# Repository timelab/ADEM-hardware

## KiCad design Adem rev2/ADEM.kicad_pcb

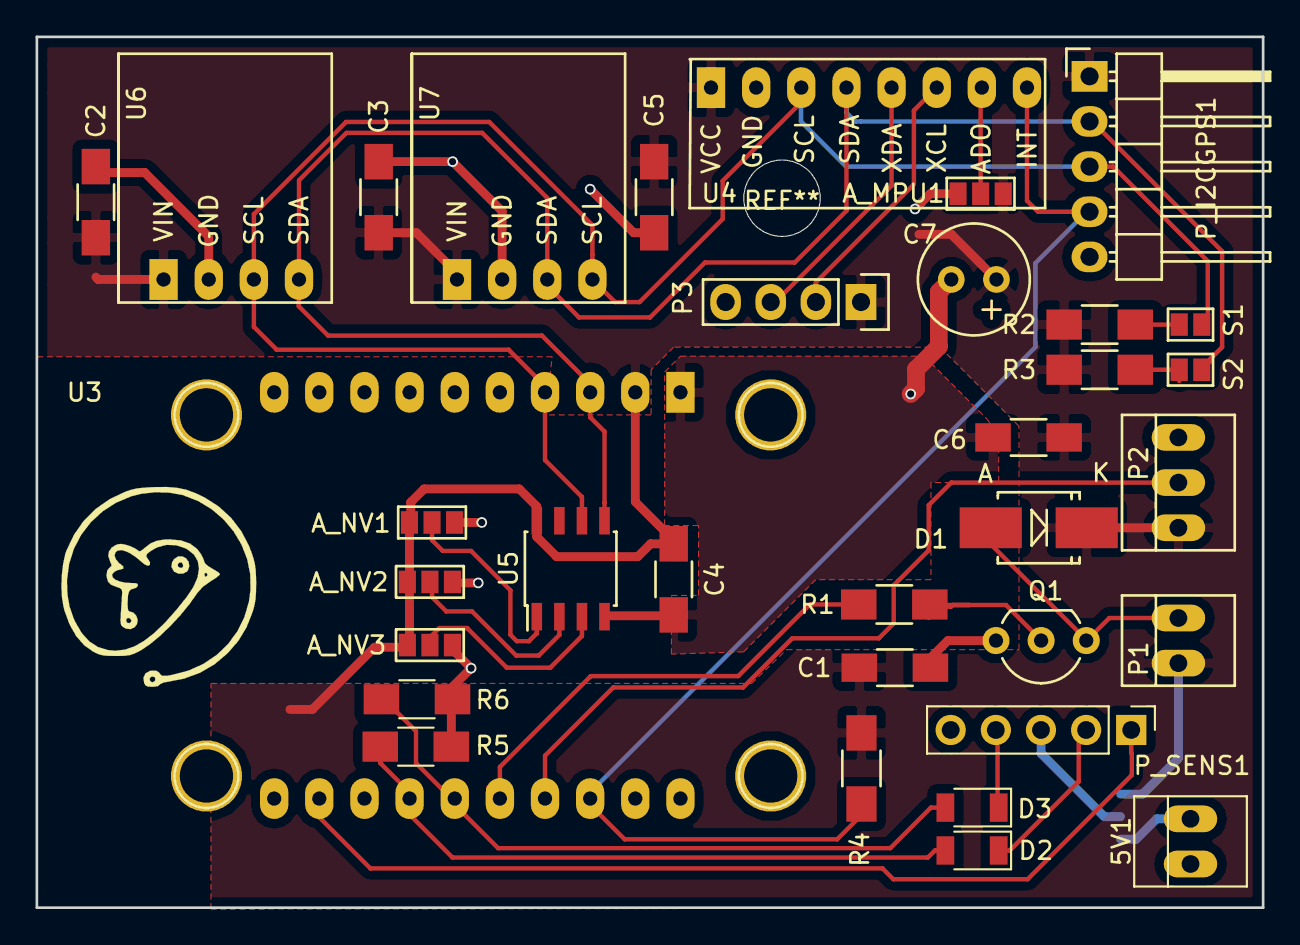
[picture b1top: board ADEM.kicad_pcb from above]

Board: 2 copper layers, 69.0 x 49.0 mm, 35 parts (1 on the bottom side), 24 nets.

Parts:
5V1: 5V; PINHEAD1-2
A_MPU1: GS_A0; GS3
A_NV1: GS_A0; GS3
A_NV2: GS_A1; GS3
A_NV3: GS_A2; GS3
C1, C2, C3, C4, C5, C6: C; C_1206_HandSoldering
C7: CP; Elko_vert_11.2x6.3mm_RM2.5
D1: DIODE; SMB_Handsoldering
D2, D3: 1V8; D_1206
P1: CONN_buzz; PINHEAD1-2
P2: CONN_01X03; PINHEAD1-3
P3: CONN_01X04; Pin_Header_Straight_1x04
P_I2CGPS1: CONN_01X05; Pin_Header_Angled_1x05
P_SENS1: CONN_01X05; Pin_Header_Straight_1x05_Pitch2.54mm
Q1: NPN; TO-92_Inline_Wide
R1, R2, R3, R4: R; R_1206_HandSoldering
R5, R6: 10K; R_1206_HandSoldering
S1: S1; GS2
S2: S2; GS2
U3: ESP8266_THING
U4: MPU6050; MPU6050_angled
U5: NVSRAM; SOIC-8_3.9x4.9mm_Pitch1.27mm
U6: BMP180
U7: HTU21D
VCC_SEL1: GS_VCC; GS3

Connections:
A_SENSOR: P_SENS1.1, U3.12
BUZZ: R1.1, U3.16
GND: 5V1.1, A_MPU1.3, A_NV1.3, A_NV2.3, A_NV3.3, C1.2, C2.2, C3.2, C4.2, C5.2, C6.2, C7.2, P2.3, P3.4, P_I2CGPS1.5, P_SENS1.5, Q1.3, R5.2, R6.2, U3.1, U3.10, U3.20, U4.2, U5.4, U6.2, U7.2
INT: P_I2CGPS1.4, R4.2, U3.18, U4.8
NEO_PXL: P2.2, U3.17
unnamed: 5V1.2, VCC_SEL1.3
unnamed: A_MPU1.2, U4.7
unnamed: A_NV1.2, U5.1
unnamed: A_NV2.2, U5.2
unnamed: A_NV3.2, U5.3
unnamed: D1.2, P1.2, Q1.1
unnamed: P3.2, U4.6
unnamed: P3.3, U4.5
unnamed: P_SENS1.3, VCC_SEL1.2
unnamed: Q1.2, R1.2
unnamed: R2.2, S1.1
unnamed: R3.1, S2.2
P10_SENS: D2.1, P_SENS1.2
P10_SENS_SHFT: D2.2, R5.1, U3.14
P25_SENS: D3.1, P_SENS1.4
P25_SENS_SHFT: D3.2, R6.1, U3.15
SCL: P_I2CGPS1.3, S1.2, U3.4, U4.3, U5.6, U6.3, U7.4
SDA: P_I2CGPS1.2, S2.1, U3.3, U4.4, U5.5, U6.4, U7.3
VCC: A_MPU1.1, A_NV1.1, A_NV2.1, A_NV3.1, C1.1, C2.1, C3.1, C4.1, C5.1, C6.1, C7.1, D1.1, P1.1, P2.1, P3.1, P_I2CGPS1.1, R2.1, R3.2, R4.1, U3.2, U4.1, U5.8, U6.1, U7.1, VCC_SEL1.1

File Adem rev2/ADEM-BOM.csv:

"Id";"Designator";"Package";"Quantity";"Designation";"Supplier and ref";
1;"U3";"ESP8266_THING";1;"ESP8266_THING";;;
2;"REF**";"MountingHole_4.3mm_M4";1;"MountingHole_4.3mm_M4";;;
3;"U7";"HTU21D";1;"HTU21D";;;
4;"R3,R1,R2,R4";"R_1206_HandSoldering";4;"R";;;
5;"C1,C2,C3,C4,C5,C6";"C_1206_HandSoldering";6;"C";;;
6;"D1";"SMB_Handsoldering";1;"DIODE";;;
7;"P1";"PINHEAD1-2";1;"CONN_buzz";;;
8;"Q1";"TO-92_Inline_Wide";1;"NPN";;;
9;"U5";"SOIC-8_3.9x4.9mm_Pitch1.27mm";1;"NVSRAM";;;
10;"U6";"BMP180";1;"BMP180";;;
11;"P2";"PINHEAD1-3";1;"CONN_01X03";;;
12;"P3";"Pin_Header_Straight_1x04";1;"CONN_01X04";;;
13;"C7";"Elko_vert_11.2x6.3mm_RM2.5";1;"CP";;;
14;"S2";"GS2";1;"S2";;;
15;"P_I2CGPS1";"Pin_Header_Angled_1x05";1;"CONN_01X05";;;
16;"A_MPU1,A_NV1";"GS3";2;"GS_A0";;;
17;"A_NV2";"GS3";1;"GS_A1";;;
18;"A_NV3";"GS3";1;"GS_A2";;;
19;"S1";"GS2";1;"S1";;;
20;"U4";"MPU6050_angled";1;"MPU6050";;;
21;"";"adem_logo";1;"";;;
22;"";"adem_logo-txt_17_B_silk";1;"";;;
23;"5V1";"PINHEAD1-2";1;"5V";;;
24;"D2,D3";"D_1206";2;"1V8";;;
25;"R5,R6";"R_1206_HandSoldering";2;"10K";;;
26;"P_SENS1";"Pin_Header_Straight_1x05_Pitch2.54mm";1;"CONN_01X05";;;
27;"VCC_SEL1";"GS3";1;"GS_VCC";;;

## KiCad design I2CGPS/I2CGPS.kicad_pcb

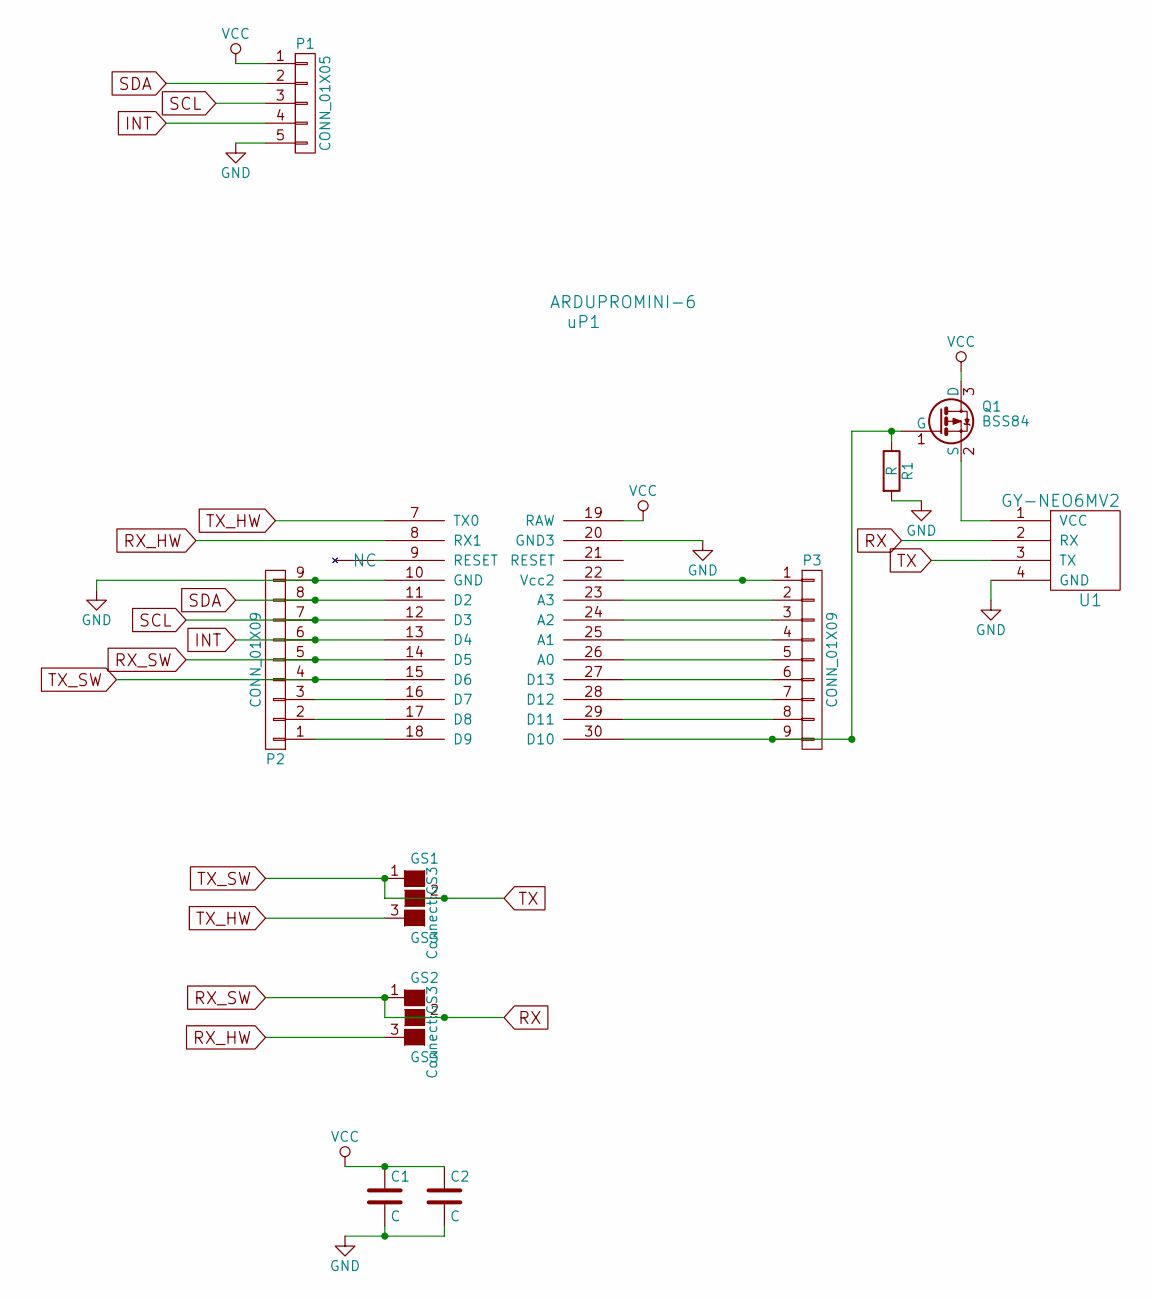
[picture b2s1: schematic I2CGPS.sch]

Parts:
C1, C2: C; C_1210_HandSoldering
GS1, GS2: GS3
P1: CONN_01X05; Pin_Header_Angled_1x05
P2, P3: CONN_01X09; Pin_Header_Straight_1x09
Q1: BSS84; SOT-23
R1: R; R_1210_HandSoldering
U1: GY-NEO6MV2
uP1: ARDUPROMINI-6; ArduProMini

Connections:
GND: C1.2, C2.2, P1.5, P2.9, R1.2, U1.4 (GND), uP1.10 (GND), uP1.20 (GND3)
INT: P1.4, P2.6, uP1.13 (D4)
unnamed: P2.1, uP1.18 (D9)
unnamed: P2.2, uP1.17 (D8)
unnamed: P2.3, uP1.16 (D7)
unnamed: P3.1, uP1.22 (Vcc2)
unnamed: P3.2, uP1.23 (A3)
unnamed: P3.3, uP1.24 (A2)
unnamed: P3.4, uP1.25 (A1)
unnamed: P3.5, uP1.26 (A0)
unnamed: P3.6, uP1.27 (D13)
unnamed: P3.7, uP1.28 (D12)
unnamed: P3.8, uP1.29 (D11)
unnamed: P3.9, Q1.1 (G), R1.1, uP1.30 (D10)
unnamed: Q1.2 (S), U1.1 (VCC)
RX: GS2.1 (G1), GS2.2 (G2), P2.5, U1.2 (RX), uP1.14 (D5)
RX_HW: GS2.3 (G3), uP1.8 (RX1)
SCL: P1.3, P2.7, uP1.12 (D3)
SDA: P1.2, P2.8, uP1.11 (D2)
TX: GS1.1 (G1), GS1.2 (G2), P2.4, U1.3 (TX), uP1.15 (D6)
TX_HW: GS1.3 (G3), uP1.7 (TX0)
VCC: C1.1, C2.1, P1.1, Q1.3 (D), uP1.19 (RAW)

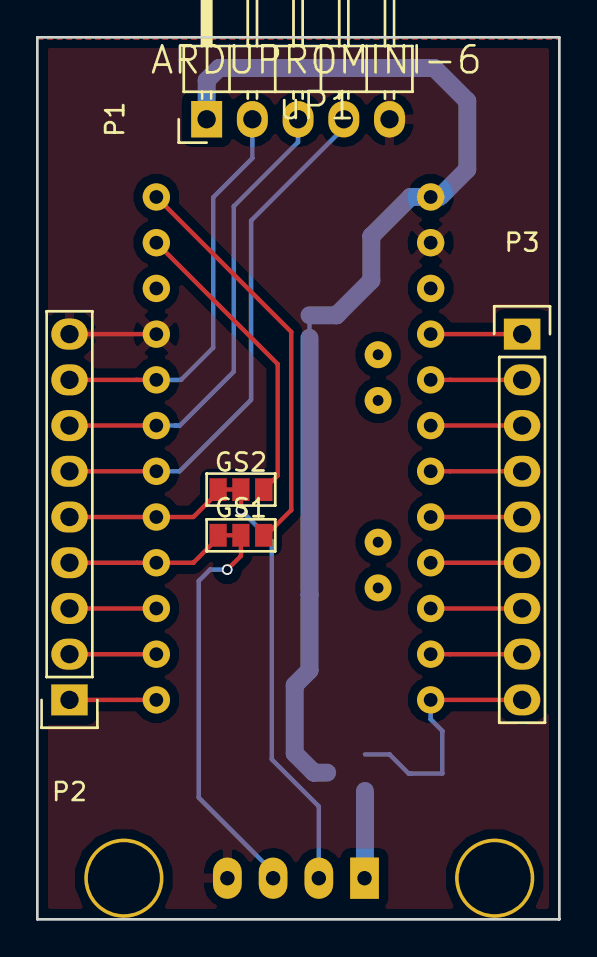
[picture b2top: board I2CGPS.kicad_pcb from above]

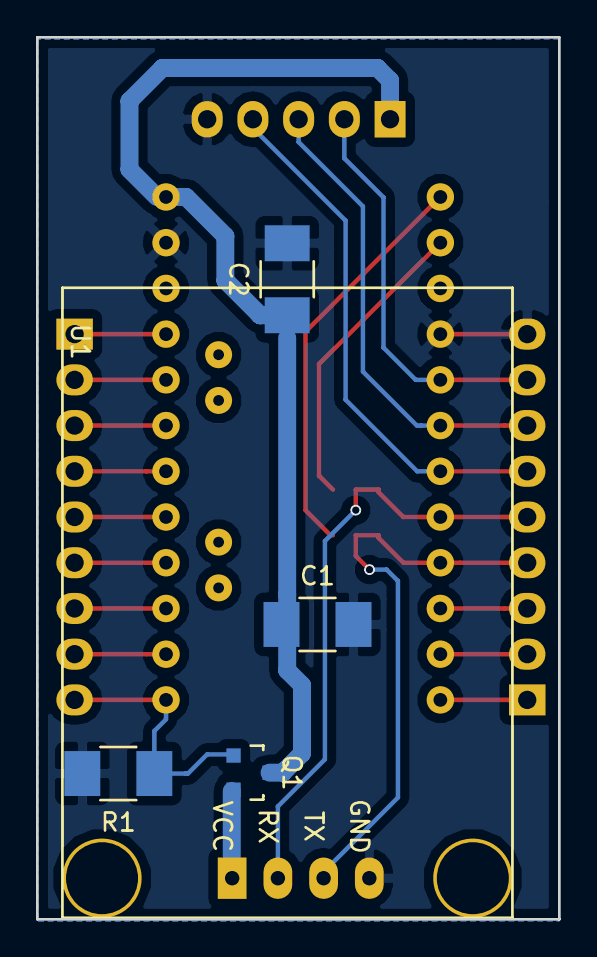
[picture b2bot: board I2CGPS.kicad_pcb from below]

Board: 2 copper layers, 29.0 x 49.0 mm, 11 parts (5 on the bottom side), 22 nets.

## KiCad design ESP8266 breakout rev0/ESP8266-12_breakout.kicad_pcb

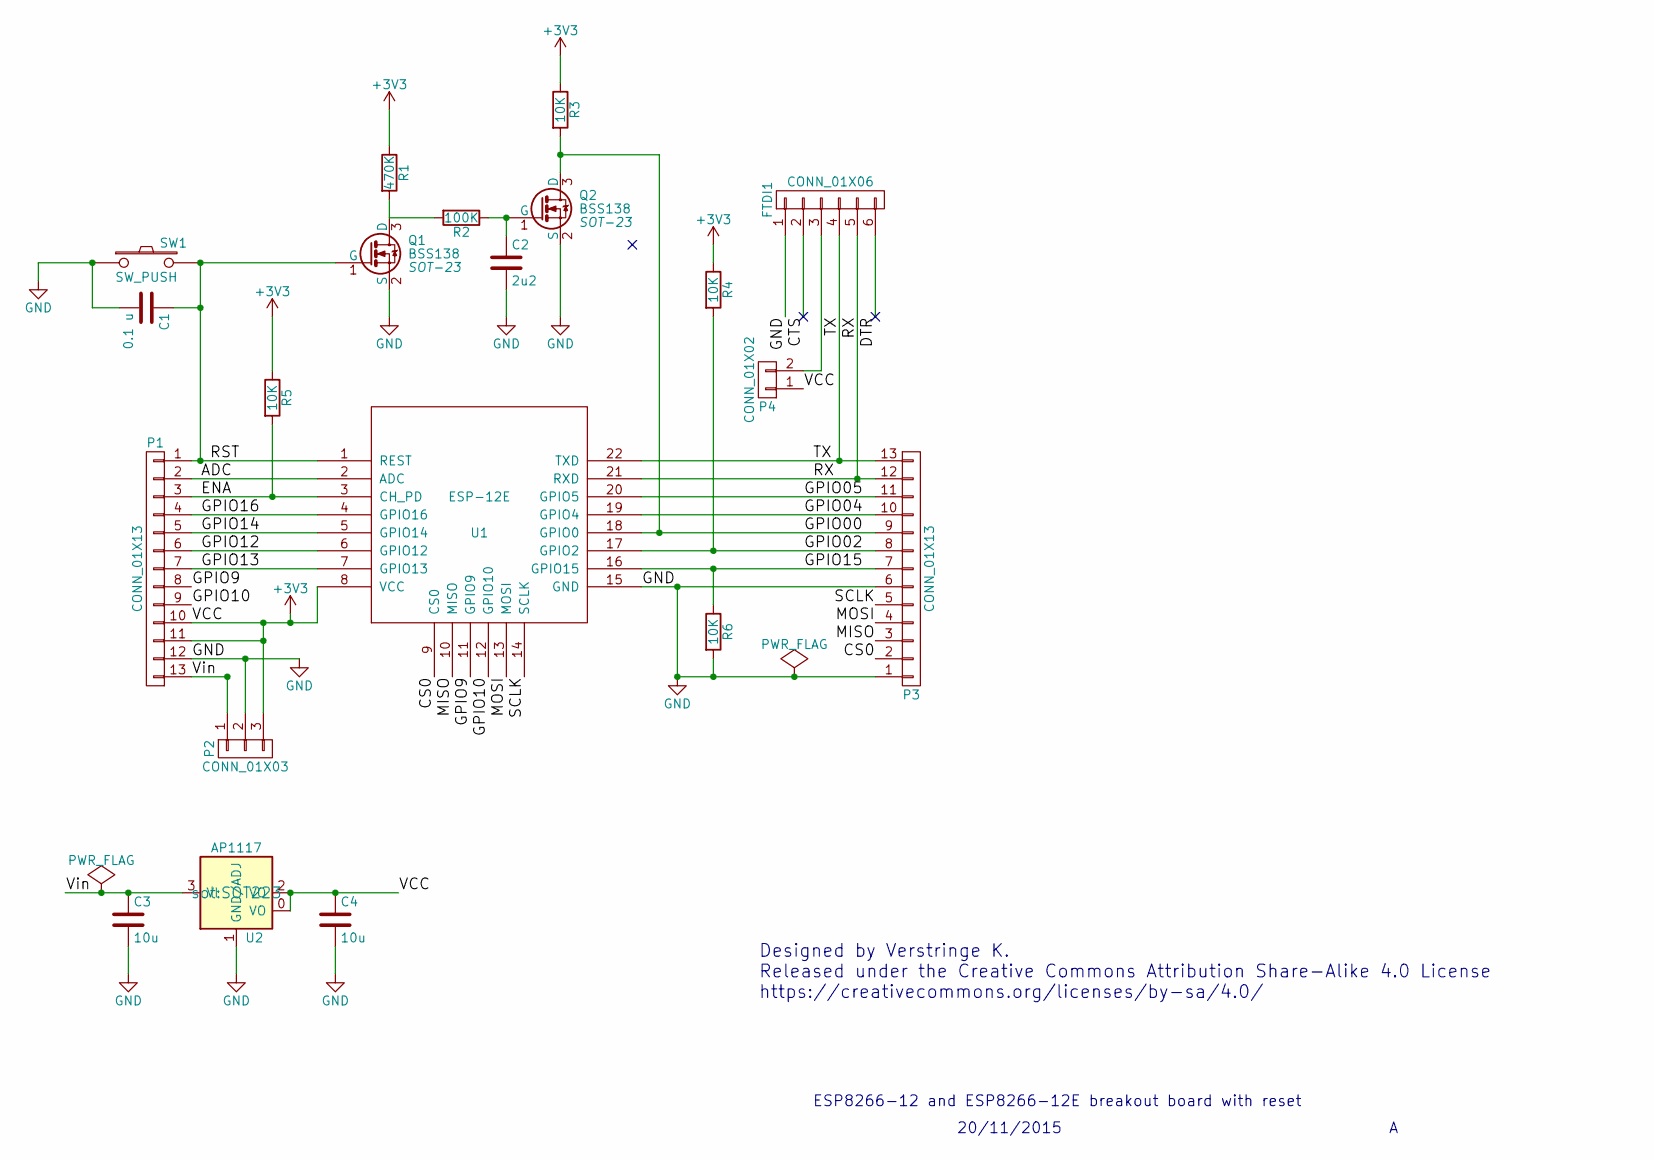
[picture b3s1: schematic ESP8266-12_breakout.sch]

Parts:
C1: 0.1 u; C_1206_HandSoldering
C2: 2u2; C_1206_HandSoldering
C3, C4: 10u; C_1206_HandSoldering
FTDI1: CONN_01X06; Pin_Header_Straight_1x06
P1, P3: CONN_01X13; Pin_Header_Straight_1x13
P2: CONN_01X03; Pin_Header_Straight_1x03
P4: CONN_01X02; Pin_Header_Straight_1x02
Q1, Q2: BSS138; SOT-23
R1: 470K; R_1206_HandSoldering
R2: 100K; R_1206_HandSoldering
R3, R4, R5, R6: 10K; R_1206_HandSoldering
SW1: SW_PUSH; SW_SPST_EVPBF
U1: ESP-12E
U2: AP1117; SOT223

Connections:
+3V3: C4.1, P1.10, P1.11, P2.3, P4.1, R1.1, R3.1, R4.1, R5.1, U1.8 (VCC), U2.0 (VO), U2.2 (VO)
/ADC: P1.2, U1.2 (ADC)
/CS0: P3.2, U1.9 (CS0)
/CTS: FTDI1.2
/DTR: FTDI1.6
/ENA: P1.3, R5.2, U1.3 (CH_PD)
/GPIO00: P3.9, Q2.3 (D), R3.2, U1.18 (GPIO0)
/GPIO02: P3.8, R4.2, U1.17 (GPIO2)
/GPIO04: P3.10, U1.19 (GPIO4)
/GPIO05: P3.11, U1.20 (GPIO5)
/GPIO9: P1.8, U1.11 (GPIO9)
/GPIO10: P1.9, U1.12 (GPIO10)
/GPIO12: P1.6, U1.6 (GPIO12)
/GPIO13: P1.7, U1.7 (GPIO13)
/GPIO14: P1.5, U1.5 (GPIO14)
/GPIO15: P3.7, R6.1, U1.16 (GPIO15)
/GPIO16: P1.4, U1.4 (GPIO16)
/MISO: P3.3, U1.10 (MISO)
/MOSI: P3.4, U1.13 (MOSI)
/RST: C1.1, P1.1, Q1.1 (G), SW1.2, U1.1 (REST)
/RX: FTDI1.5, P3.12, U1.21 (RXD)
/SCLK: P3.5, U1.14 (SCLK)
/TX: FTDI1.4, P3.13, U1.22 (TXD)
/Vin: C3.1, P1.13, P2.1, U2.3 (VI)
GND: C1.2, C2.2, C3.2, C4.2, FTDI1.1, P1.12, P2.2, P3.1, P3.6, Q1.2 (S), Q2.2 (S), R6.2, SW1.1, U1.15 (GND), U2.1 (GND/ADJ)
unnamed: C2.1, Q2.1 (G), R2.1
unnamed: FTDI1.3, P4.2
unnamed: Q1.3 (D), R1.2, R2.2

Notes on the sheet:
ESP8266-12 and ESP8266-12E breakout board with reset
20/11/2015
Designed by Verstringe K. Released under the Creative Commons Attribution Share-Alike 4.0 License https://creativecommons.org/licenses/by-sa/4.0/

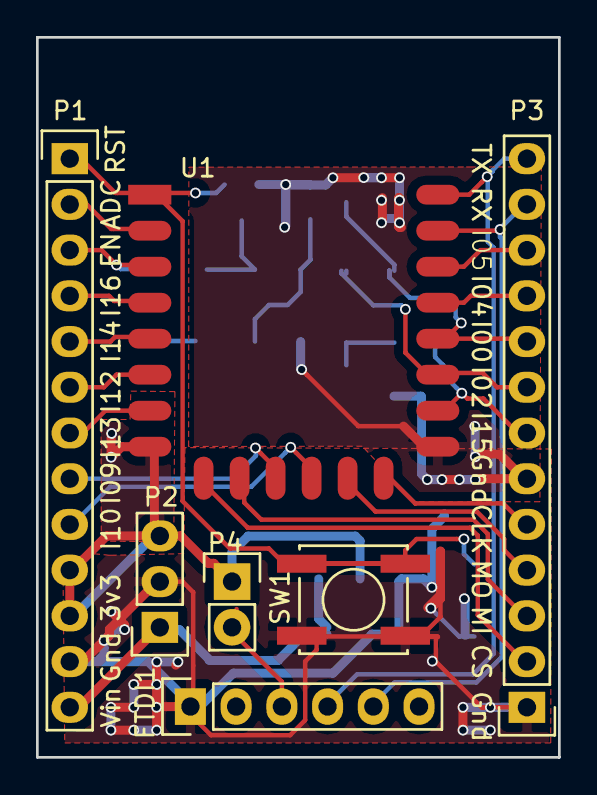
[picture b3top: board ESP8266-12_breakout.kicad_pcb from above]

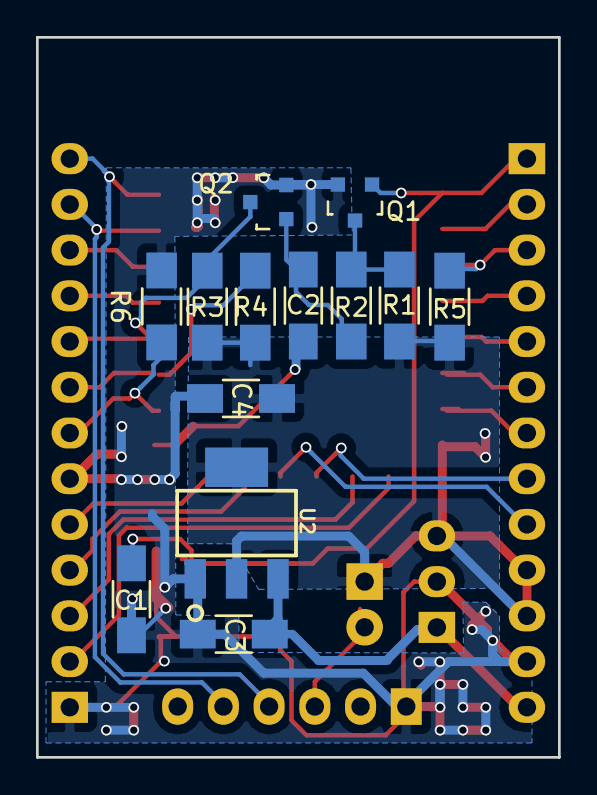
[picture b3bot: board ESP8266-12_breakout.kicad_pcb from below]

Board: 2 copper layers, 29.0 x 40.0 mm, 20 parts (13 on the bottom side), 26 nets.

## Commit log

2016-08-21 prepare hardware revision 1
2016-08-22 I2C-GPS initial design
2016-08-23 IC2 GPS with power down fet
2016-08-24 pdf prints
2016-08-27 resized to particle sensor and panelized
2016-08-27 added adem logo's
2016-09-01 added mounting hole and fixed footprint error
2016-11-01 added softserial to board
    allows selection of hardware serial or soft serial by solder selector
2017-09-14 alfa prototype
    updated for first pcb prototype
2017-09-27 Added Bill Of Materials
2017-09-27 Added BOMs created with KiCad_BOM_Wizard
